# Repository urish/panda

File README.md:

# panda

[CrossFit Panda](https://www.crossfitpanda.com/) Logo PCB, with eye that glow red when you touch it. Designed with [KiCad](http://kicad.org/), manufactured by [PCBWay](https://www.pcbway.com).

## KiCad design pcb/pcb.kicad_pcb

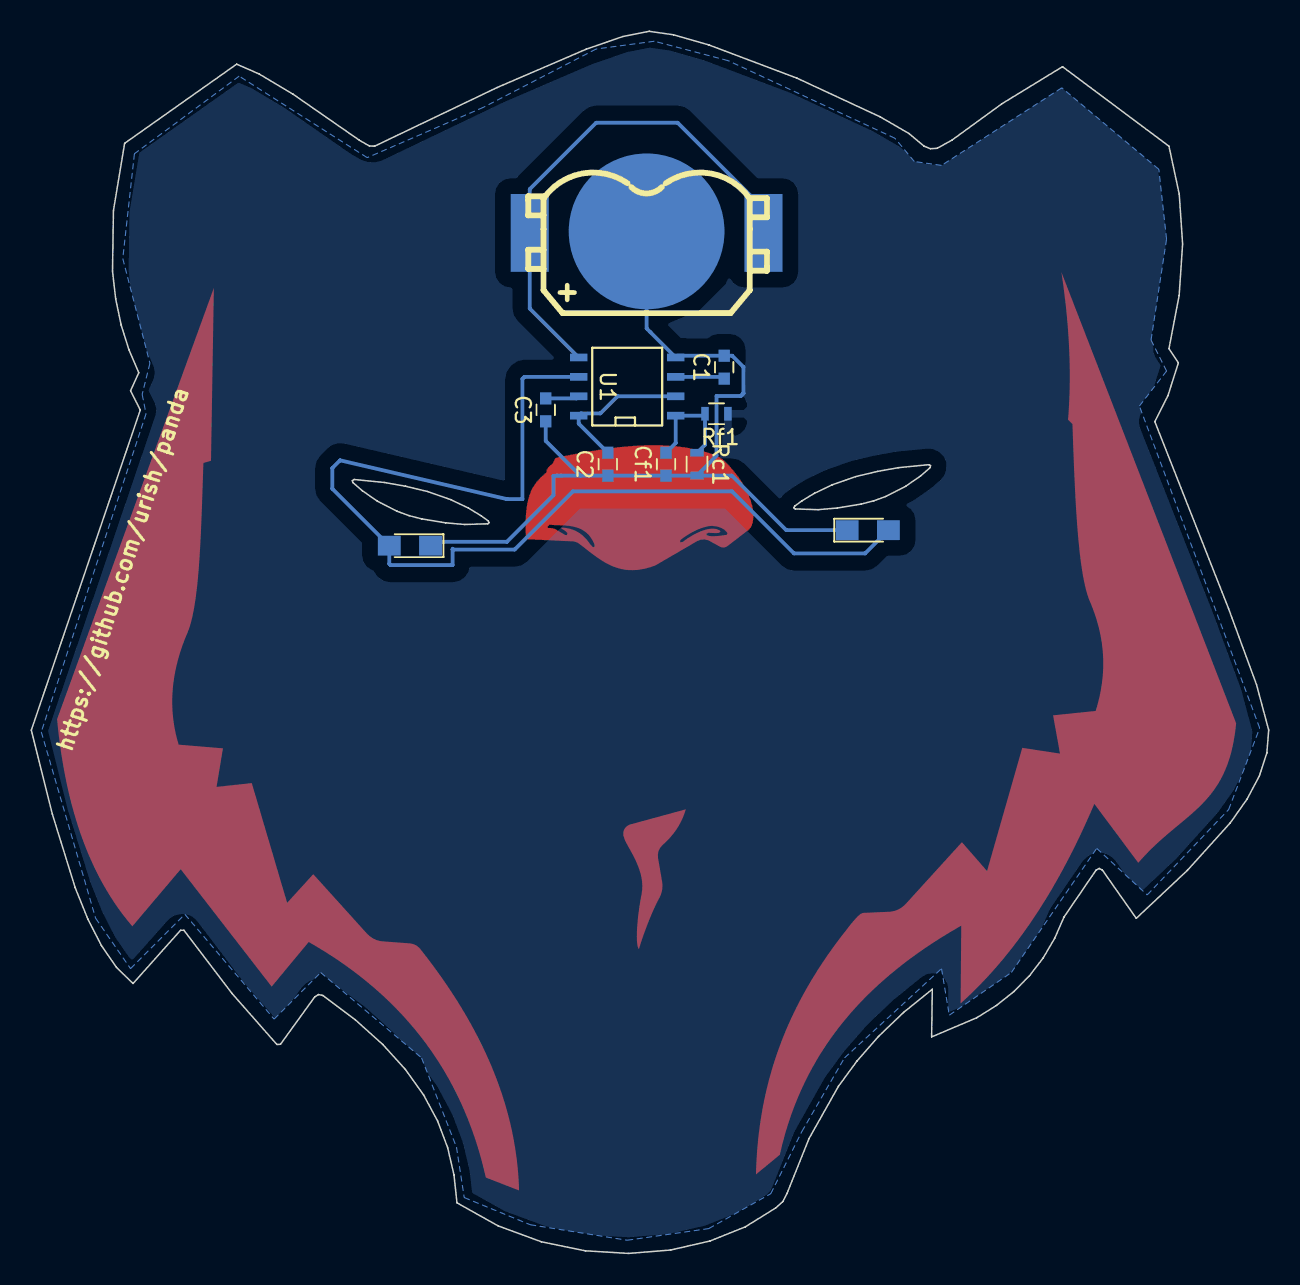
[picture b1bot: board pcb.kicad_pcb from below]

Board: 2 copper layers, 81.0 x 80.0 mm, 11 parts (10 on the bottom side), 7 nets.

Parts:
BT1: Battery_Cell; BAT_CR1216
C1: 470nF; C_0603
C2: 100nF; C_0603
C3: 22pF; C_0603
Cf1: 10pF; C_0603
D1, D2: LED; LED_0805_HandSoldering
Rc1: 100k; R_0603
Rf1: 1k; R_0603
U1: PCF8883; SOIC-8-N
svg2mod: G***; panda

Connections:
GND: BT1.2, C1.2, C2.2, C3.1, Cf1.2, D1.1, D2.1, Rc1.1, U1.4
LEDS: D1.2, D2.2, U1.6
unnamed: C1.1, U1.3
unnamed: C3.2, U1.7
unnamed: Cf1.1, Rc1.2, Rf1.1, U1.1
VDD: BT1.1, U1.5
VREGINT: C2.1, U1.2, U1.8

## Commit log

2017-08-03 Add initial PCB
2017-08-03 add leds + capacitive switch
2017-08-03 add touch area, enlarge LEDs
2017-08-03 fix unconnected pin
2017-08-03 fix touch area, configure gerber
2017-08-03 add repo url text on bottom
2017-08-14 Add component values
2017-08-16 remove eagle files
2017-08-16 set PCF8883 to switch mode
2017-08-19 organize panda svg into layers
2021-11-07 Update KiCad link
    https://forum.kicad.info/t/warning-avoid-all-links-to-kicad-pcb-org-use-kicad-org/31521/
